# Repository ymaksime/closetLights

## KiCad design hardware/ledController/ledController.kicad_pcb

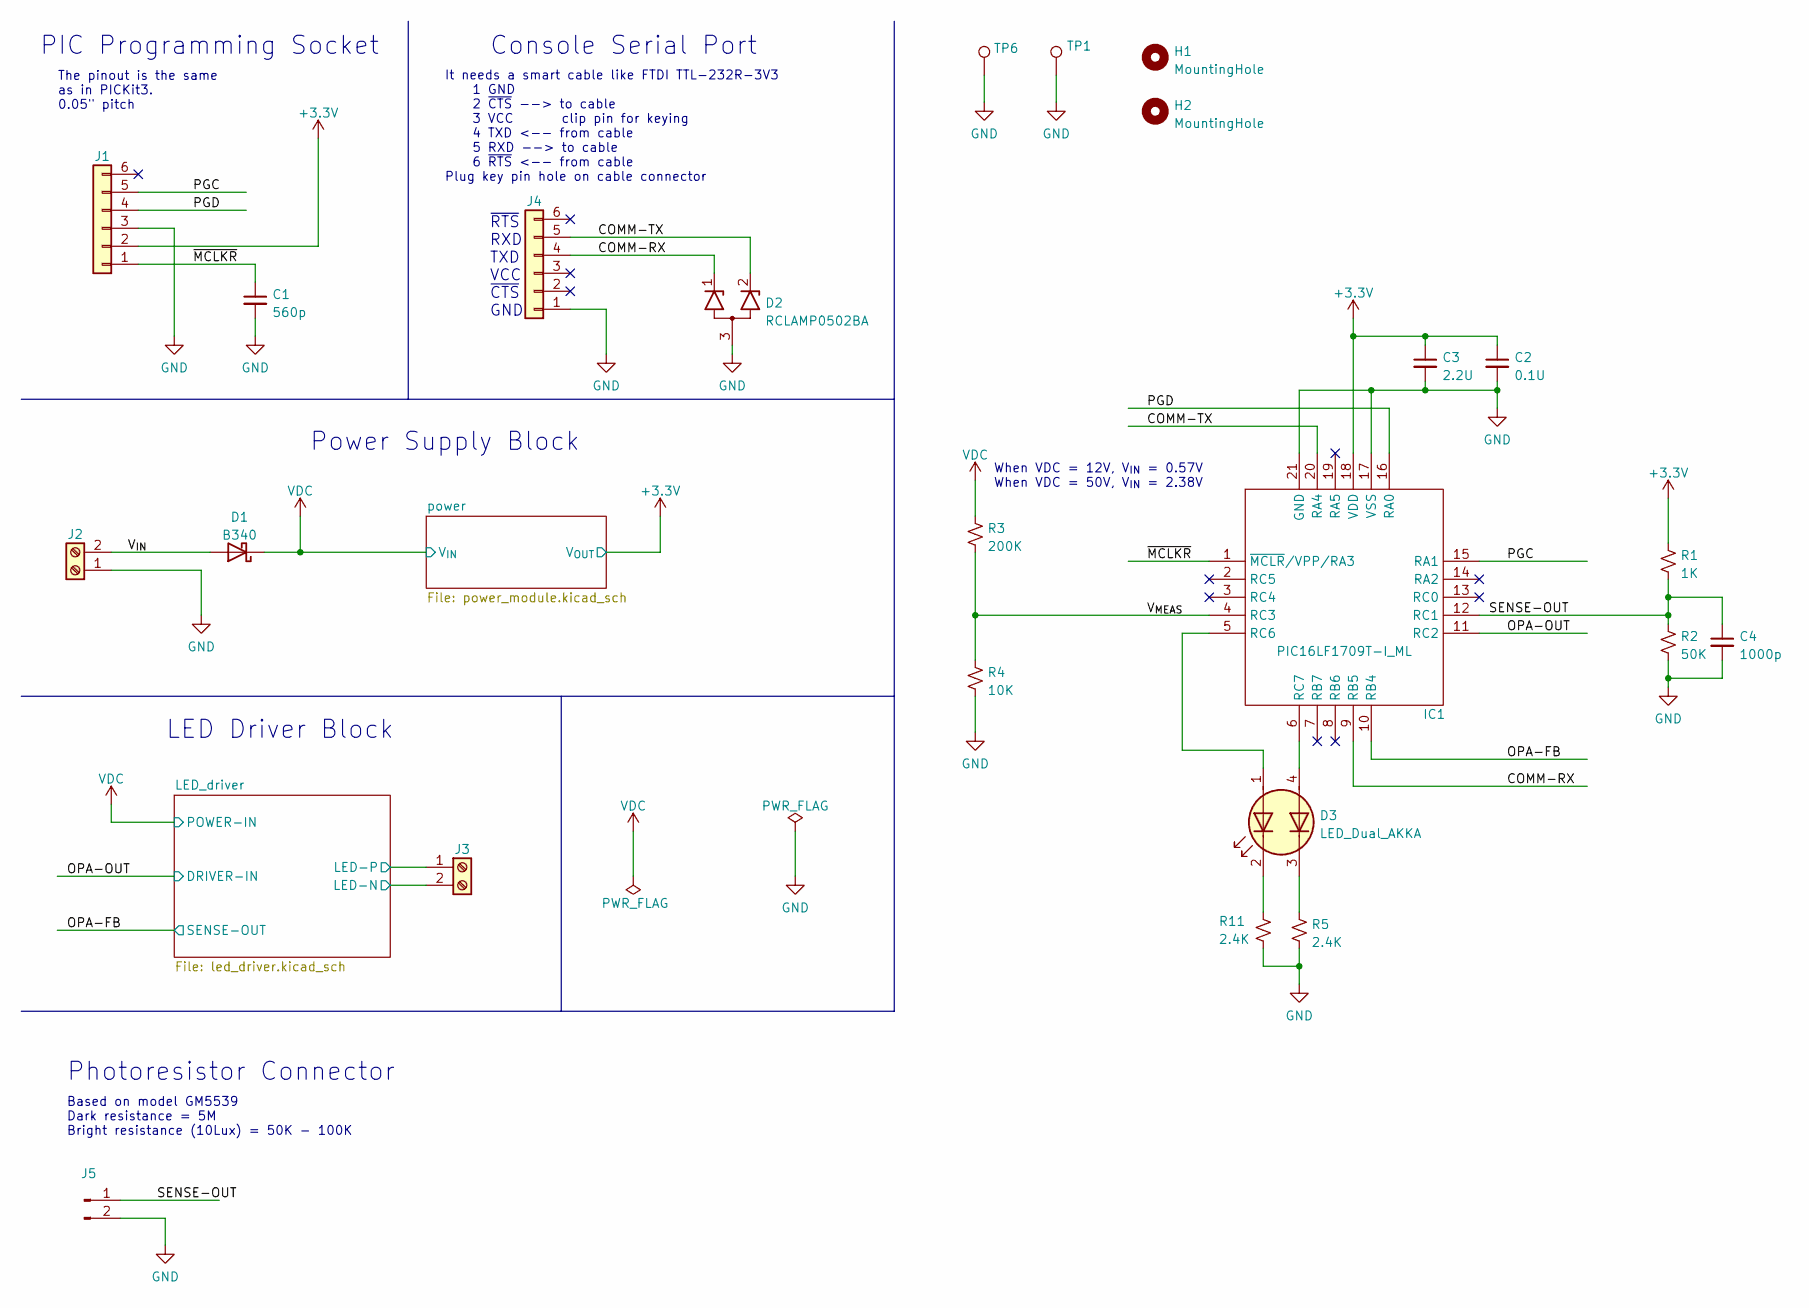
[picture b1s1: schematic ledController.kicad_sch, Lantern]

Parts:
C1: 560p; C_0402_1005Metric_Pad0.74x0.62mm_HandSolder
C2: 0.1U; C_0402_1005Metric_Pad0.74x0.62mm_HandSolder
C3: 2.2U; C_0402_1005Metric_Pad0.74x0.62mm_HandSolder
C4: 1000p; C_0402_1005Metric_Pad0.74x0.62mm_HandSolder
D1: B340; D_SMA
D2: RCLAMP0502BA; SC-75
D3: LED_Dual_AKKA; LED_Kingbright_APHBM2012_2x1.25mm
H1, H2: MountingHole; MountingHole_2.5mm_Pad_TopBottom
IC1: PIC16LF1709T-I_ML; QFN-20-1EP_4x4mm_P0.5mm_EP2.5x2.5mm
J1: Conn_01x06; PinHeader_1x06_P1.27mm_Vertical
J2, J3: Screw_Terminal_01x02; TerminalBlock_Altech_AK300-2_P5.00mm
J4: Conn_01x06; PinHeader_1x06_P2.54mm_Vertical
J5: Conn_01x02_Male; PinSocket_1x02_P2.54mm_Vertical
R1: 1K; R_0603_1608Metric_Pad0.98x0.95mm_HandSolder
R2: 50K; R_0603_1608Metric_Pad0.98x0.95mm_HandSolder
R3: 200K; R_0603_1608Metric_Pad0.98x0.95mm_HandSolder
R4: 10K; R_0603_1608Metric_Pad0.98x0.95mm_HandSolder
R5, R11: 2.4K; R_0603_1608Metric_Pad0.98x0.95mm_HandSolder
TP1, TP6: TestPoint; TestPoint_Pad_0.185in_x_0.135in

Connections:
+3.3V: C2.1, C3.1, IC1.18 (VDD), J1.2, R1.1; also elsewhere on the board
/COMM-RX: D2.1 (K1), IC1.9 (RB5), J4.4
/COMM-TX: D2.2 (K2), IC1.20 (RA4), J4.5
/LED_driver/LED-N: J3.2; also elsewhere on the board
/OPA-FB: IC1.10 (RB4); also elsewhere on the board
/OPA-OUT: IC1.11 (RC2); also elsewhere on the board
/PGC: IC1.15 (RA1), J1.5
/PGD: IC1.16 (RA0), J1.4
/SENSE-OUT: C4.1, IC1.12 (RC1), J5.1, R1.2, R2.1
/V_{IN}: D1.2 (A), J2.2
/V_{MEAS}: IC1.4 (RC3), R3.2, R4.1
/~MCLKR: C1.1, IC1.1 (~MCLR/VPP/RA3), J1.1
GND: C1.2, C2.2, C3.2, C4.2, D2.3 (A), IC1.17 (VSS), IC1.21 (GND), J1.3, J2.1, J4.1, J5.2, R2.2, R4.2, R5.2, R11.2, TP1.1, TP6.1; also elsewhere on the board
unnamed: D3.1 (A1), IC1.5 (RC6)
unnamed: D3.2 (K1), R11.1
unnamed: D3.3 (K2), R5.1
unnamed: D3.4 (A2), IC1.6 (RC7)
VDC: D1.1 (K), J3.1, R3.1; also elsewhere on the board

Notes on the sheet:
Photoresistor Connector
It needs a smart cable like FTDI TTL-232R-3V3 1 GND 2 ~{CTS} --> to cable 3 VCC clip pin for keying 4 TXD <-- from cable 5 RXD --> to cable 6 ~{RTS} <-- from cable Plug key pin hole on cable connector
~{RTS} RXD TXD VCC ~{CTS} GND
Power Supply Block
PIC Programming Socket
Console Serial Port
The pinout is the same as in PICKit3. 0.05" pitch
When VDC = 12V, V_{IN} = 0.57V When VDC = 50V, V_{IN} = 2.38V
Based on model GM5539 Dark resistance = 5M Bright resistance (10Lux) = 50K - 100K
LED Driver Block

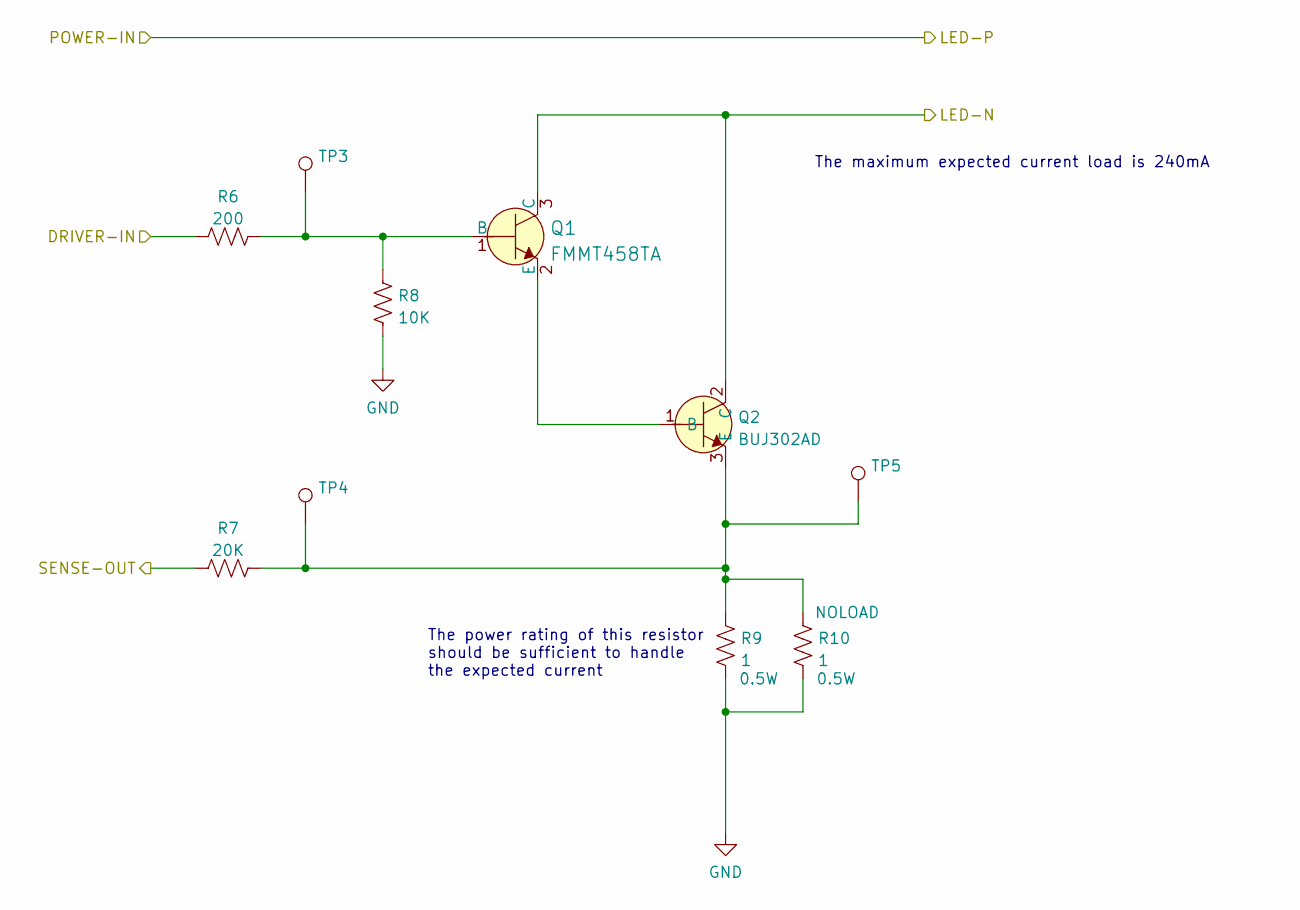
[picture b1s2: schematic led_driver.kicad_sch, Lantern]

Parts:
Q1: FMMT458TA; SOT-23-3; MPN FMMT458TA; Digi-Key_PN FMMT458CT-ND
Q2: BUJ302AD; SOT-428
R6: 200; R_0603_1608Metric_Pad0.98x0.95mm_HandSolder
R7: 20K; R_0603_1608Metric_Pad0.98x0.95mm_HandSolder
R8: 10K; R_0603_1608Metric_Pad0.98x0.95mm_HandSolder
R9, R10: 1; R_1206_3216Metric_Pad1.30x1.75mm_HandSolder
TP3, TP4, TP5: TestPoint; TestPoint_Pad_D1.5mm

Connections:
/LED_driver/LED-N: Q1.3 (C), Q2.2 (C); also elsewhere on the board
/OPA-FB: R7.1; also elsewhere on the board
/OPA-OUT: R6.1; also elsewhere on the board
GND: R8.2, R9.2, R10.2; also elsewhere on the board
unnamed: Q1.1 (B), R6.2, R8.1, TP3.1
unnamed: Q1.2 (E), Q2.1 (B)
unnamed: Q2.3 (E), R7.2, R9.1, R10.1, TP4.1, TP5.1

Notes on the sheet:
The maximum expected current load is 240mA
The power rating of this resistor should be sufficient to handle the expected current

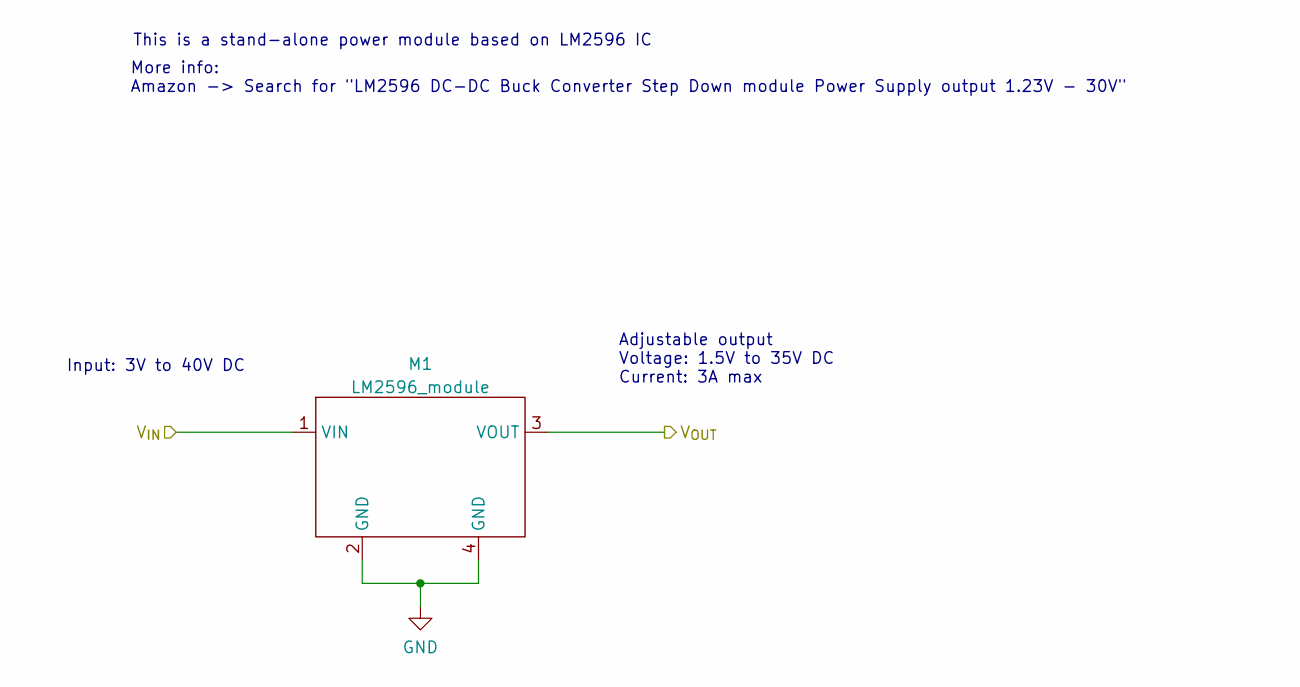
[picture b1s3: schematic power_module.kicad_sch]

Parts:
M1: LM2596_module

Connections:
+3.3V: M1.3 (VOUT); also elsewhere on the board
GND: M1.2 (GND), M1.4 (GND); also elsewhere on the board
VDC: M1.1 (VIN); also elsewhere on the board

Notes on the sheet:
Adjustable output Voltage: 1.5V to 35V DC Current: 3A max
Input: 3V to 40V DC
This is a stand-alone power module based on LM2596 IC
More info: Amazon -> Search for "LM2596 DC-DC Buck Converter Step Down module Power Supply output 1.23V - 30V"

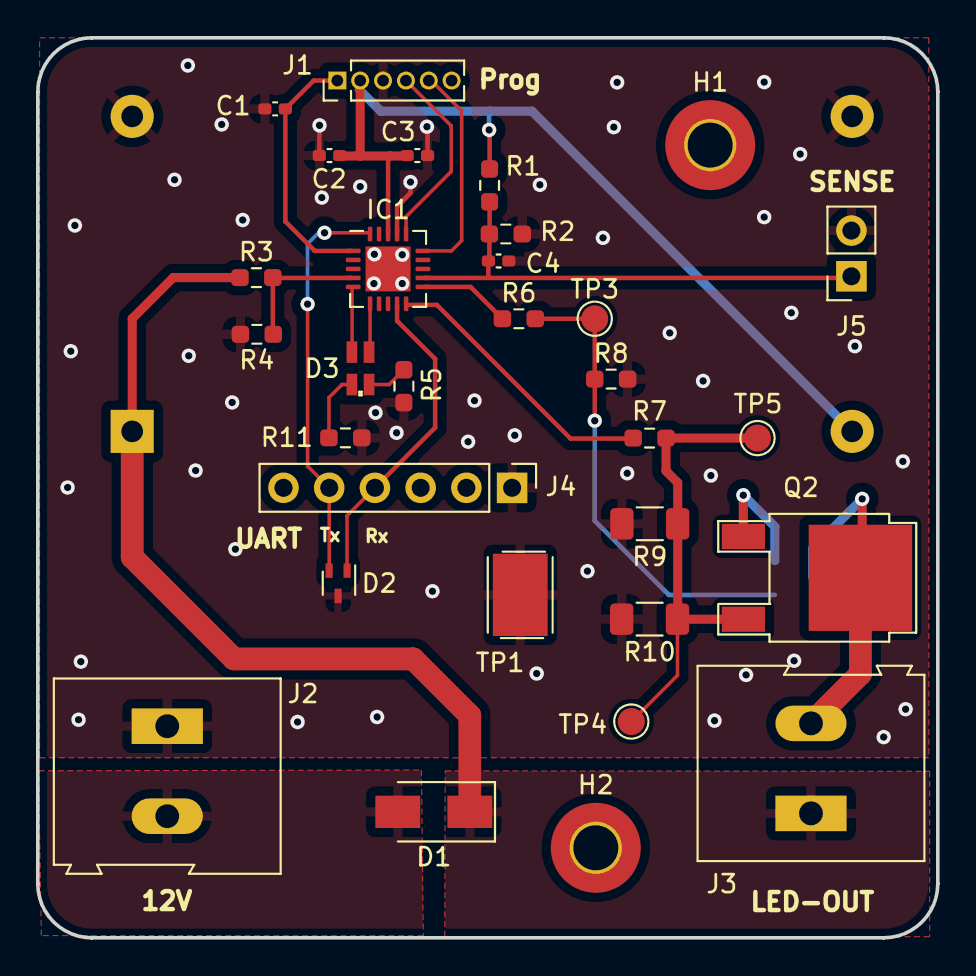
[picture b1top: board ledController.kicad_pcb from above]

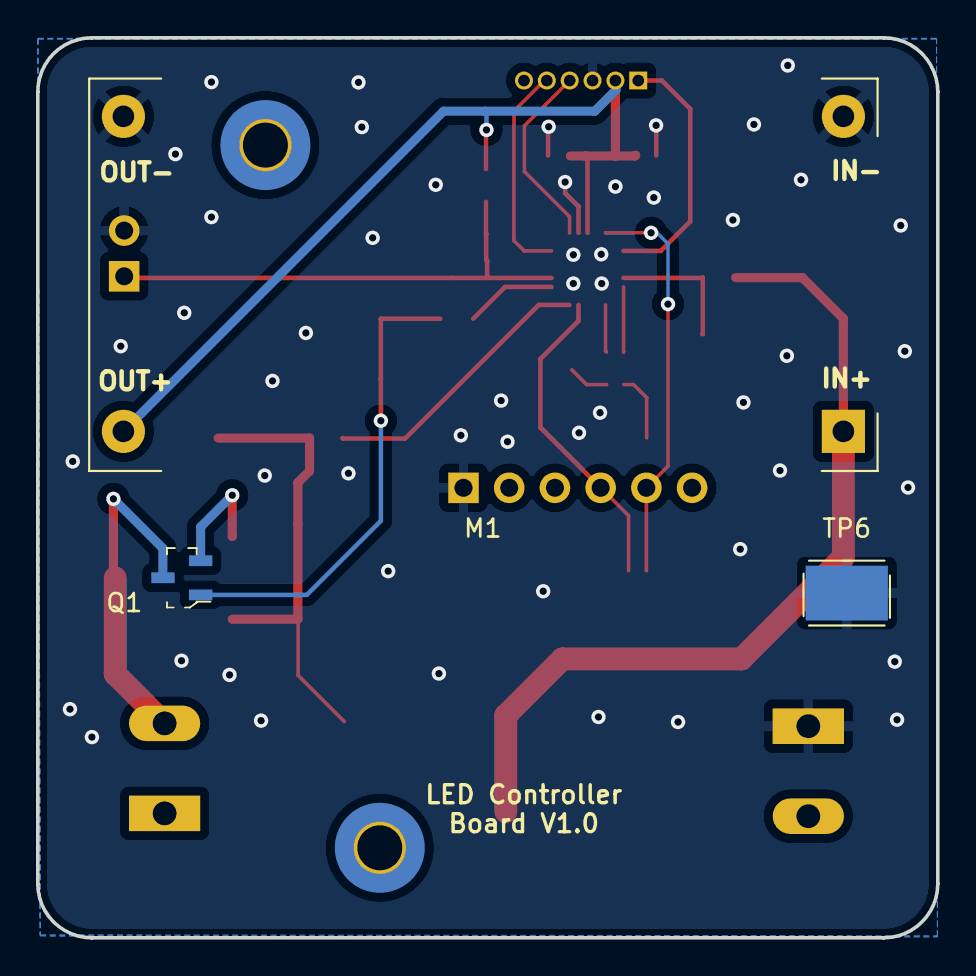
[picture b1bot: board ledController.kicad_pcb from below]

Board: 2 copper layers, 50.0 x 50.0 mm, 34 parts (3 on the bottom side), 21 nets.

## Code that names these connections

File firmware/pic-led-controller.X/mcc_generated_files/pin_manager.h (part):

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#define RA4_SetHigh()            do { LATAbits.LATA4 = 1; } while(0)
#define RA4_SetLow()             do { LATAbits.LATA4 = 0; } while(0)
#define RA4_Toggle()             do { LATAbits.LATA4 = ~LATAbits.LATA4; } while(0)
#define RA4_GetValue()              PORTAbits.RA4
#define RA4_SetDigitalInput()    do { TRISAbits.TRISA4 = 1; } while(0)
#define RA4_SetDigitalOutput()   do { TRISAbits.TRISA4 = 0; } while(0)
#define RA4_SetPullup()             do { WPUAbits.WPUA4 = 1; } while(0)
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#define RB4_SetHigh()            do { LATBbits.LATB4 = 1; } while(0)
#define RB4_SetLow()             do { LATBbits.LATB4 = 0; } while(0)
#define RB4_Toggle()             do { LATBbits.LATB4 = ~LATBbits.LATB4; } while(0)
#define RB4_GetValue()              PORTBbits.RB4
#define RB4_SetDigitalInput()    do { TRISBbits.TRISB4 = 1; } while(0)
#define RB4_SetDigitalOutput()   do { TRISBbits.TRISB4 = 0; } while(0)
#define RB4_SetPullup()             do { WPUBbits.WPUB4 = 1; } while(0)
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#define RB5_SetHigh()            do { LATBbits.LATB5 = 1; } while(0)
#define RB5_SetLow()             do { LATBbits.LATB5 = 0; } while(0)
#define RB5_Toggle()             do { LATBbits.LATB5 = ~LATBbits.LATB5; } while(0)
#define RB5_GetValue()              PORTBbits.RB5
#define RB5_SetDigitalInput()    do { TRISBbits.TRISB5 = 1; } while(0)
#define RB5_SetDigitalOutput()   do { TRISBbits.TRISB5 = 0; } while(0)
#define RB5_SetPullup()             do { WPUBbits.WPUB5 = 1; } while(0)
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// get/set sensor aliases
#define sensor_TRIS                 TRISCbits.TRISC1
#define sensor_LAT                  LATCbits.LATC1
#define sensor_PORT                 PORTCbits.RC1
#define sensor_WPU                  WPUCbits.WPUC1
#define sensor_OD                   ODCONCbits.ODC1
#define sensor_ANS                  ANSELCbits.ANSC1
#define sensor_SetHigh()            do { LATCbits.LATC1 = 1; } while(0)
#define sensor_SetLow()             do { LATCbits.LATC1 = 0; } while(0)
#define sensor_Toggle()             do { LATCbits.LATC1 = ~LATCbits.LATC1; } while(0)
#define sensor_GetValue()           PORTCbits.RC1
#define sensor_SetDigitalInput()    do { TRISCbits.TRISC1 = 1; } while(0)
#define sensor_SetDigitalOutput()   do { TRISCbits.TRISC1 = 0; } while(0)
#define sensor_SetPullup()          do { WPUCbits.WPUC1 = 1; } while(0)
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#define RC2_SetHigh()            do { LATCbits.LATC2 = 1; } while(0)
#define RC2_SetLow()             do { LATCbits.LATC2 = 0; } while(0)
#define RC2_Toggle()             do { LATCbits.LATC2 = ~LATCbits.LATC2; } while(0)
#define RC2_GetValue()              PORTCbits.RC2
#define RC2_SetDigitalInput()    do { TRISCbits.TRISC2 = 1; } while(0)
#define RC2_SetDigitalOutput()   do { TRISCbits.TRISC2 = 0; } while(0)
#define RC2_SetPullup()             do { WPUCbits.WPUC2 = 1; } while(0)
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// get/set vMeas aliases
#define vMeas_TRIS                 TRISCbits.TRISC3
#define vMeas_LAT                  LATCbits.LATC3
#define vMeas_PORT                 PORTCbits.RC3
#define vMeas_WPU                  WPUCbits.WPUC3
#define vMeas_OD                   ODCONCbits.ODC3
#define vMeas_ANS                  ANSELCbits.ANSC3
#define vMeas_SetHigh()            do { LATCbits.LATC3 = 1; } while(0)
#define vMeas_SetLow()             do { LATCbits.LATC3 = 0; } while(0)
#define vMeas_Toggle()             do { LATCbits.LATC3 = ~LATCbits.LATC3; } while(0)
#define vMeas_GetValue()           PORTCbits.RC3
#define vMeas_SetDigitalInput()    do { TRISCbits.TRISC3 = 1; } while(0)
#define vMeas_SetDigitalOutput()   do { TRISCbits.TRISC3 = 0; } while(0)
#define vMeas_SetPullup()          do { WPUCbits.WPUC3 = 1; } while(0)
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// get/set ledRed aliases
#define ledRed_TRIS                 TRISCbits.TRISC6
#define ledRed_LAT                  LATCbits.LATC6
#define ledRed_PORT                 PORTCbits.RC6
#define ledRed_WPU                  WPUCbits.WPUC6
#define ledRed_OD                   ODCONCbits.ODC6
#define ledRed_ANS                  ANSELCbits.ANSC6
#define ledRed_SetHigh()            do { LATCbits.LATC6 = 1; } while(0)
#define ledRed_SetLow()             do { LATCbits.LATC6 = 0; } while(0)
#define ledRed_Toggle()             do { LATCbits.LATC6 = ~LATCbits.LATC6; } while(0)
#define ledRed_GetValue()           PORTCbits.RC6
#define ledRed_SetDigitalInput()    do { TRISCbits.TRISC6 = 1; } while(0)
#define ledRed_SetDigitalOutput()   do { TRISCbits.TRISC6 = 0; } while(0)
#define ledRed_SetPullup()          do { WPUCbits.WPUC6 = 1; } while(0)
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// get/set ledGrn aliases
#define ledGrn_TRIS                 TRISCbits.TRISC7
#define ledGrn_LAT                  LATCbits.LATC7
#define ledGrn_PORT                 PORTCbits.RC7
#define ledGrn_WPU                  WPUCbits.WPUC7
#define ledGrn_OD                   ODCONCbits.ODC7
#define ledGrn_ANS                  ANSELCbits.ANSC7
#define ledGrn_SetHigh()            do { LATCbits.LATC7 = 1; } while(0)
#define ledGrn_SetLow()             do { LATCbits.LATC7 = 0; } while(0)
#define ledGrn_Toggle()             do { LATCbits.LATC7 = ~LATCbits.LATC7; } while(0)
#define ledGrn_GetValue()           PORTCbits.RC7
#define ledGrn_SetDigitalInput()    do { TRISCbits.TRISC7 = 1; } while(0)
#define ledGrn_SetDigitalOutput()   do { TRISCbits.TRISC7 = 0; } while(0)
#define ledGrn_SetPullup()          do { WPUCbits.WPUC7 = 1; } while(0)
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
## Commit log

2022-09-26 initial board checkin
2022-09-26 more files to ignore
2022-09-26 info about additional libriries
2022-10-06 Some technical info about the LED strip light
2022-10-06 Added two more schematic pages
2022-10-07 Updated max LED current
2022-10-07 Added LTSpice simulations current driver
2022-10-07 Added theoretical ON resistance at max current
2022-10-10 Updated library tables to include custom library
2022-10-14 Few mods to the simulation files
2022-10-14 Added new schematic page for led current driver
2022-10-14 Incorporated the led driver to the main design
2022-10-21 Added serial comm
2022-10-27 Renamed and modified power sheet
2022-10-27 Added one more design for 3.3V switcher
2022-10-27 Some cleanup
2022-10-27 Added BJT base resistor and some cleanup
2022-10-27 Putting everything together
2022-11-01 Added NOLOAD resistor R10
2022-12-09 Added a datasheet for PIR censor
2022-12-09 Update gitignore
2022-12-21 Added new schematic for power module
2022-12-21 First attempt of schematic to PCB
2022-12-29 More schematic updates
    Moved from PIR sensor to photoresistor + additional components
    Added mounting holes
    Moved to a stand alone 3.3V switcher
2022-12-29 PCB work
2022-12-29 Minor changes
2022-12-29 Changed R9 and R10 to use 1206
2022-12-29 Replaced debug LED
2022-12-30 modified footprint for D1
2022-12-30 Replaced footprint of D2
2022-12-30 Changed based on the footprint updates
2022-12-30 Minor changes in the simulations
2023-01-06 Initial commit for PIC firmware
2023-01-09 Device change
    Changed from PIC16F1769 to PIC16LF1709
2023-01-09 New datasheets
2023-01-10 Version V1.1
    Replaced PIC16F1769 with PIC16LF1709. They are pin-to-pin
    compatible with each other
2023-04-05 Added support for RS232 communication
    Also added a few function to control LEDs and read ADC channels
    for sensor and +12V voltage
2023-04-05 Fixed the note for Serial Port connector
2023-04-05 Changed R1 from 1K to 15K
    Based on the experiments, R1 needs to be close to 15K
2023-04-12 Added support for ADC read functions
    Added the following RS232 functions
    ADC5
    * Sets channel 5 as an active ADC channel
    * This channel measure SENSOR-OUT signal, which is photo-resistor
    output
    ADC7
2023-08-31 Added DAC control functions
    DACS
    Allows a user to set DAC to a specific value through RS232 interface.
    The value must be in decimal format and should not exceed 8-bit value
    If larger than an 8-bit value, it will be truncated
    Expected command format: DACS XXX
    DACR
2023-08-31 Function name change
    Renamed "read_millivolts()" to "adc_read" since it is just averaged out
    ADC reading
2023-09-01 Forgot to include for DAC
2023-09-01 Better comments with formula
2023-09-01 Initial work PV scripts
2023-09-05 Store only valid characters
2023-09-05 Added ECHO command
    When interfacing with the module using python scripts, we need to turn
    OFF the echo feature otherwise it becomes difficult to parse the output
2023-09-05 forgot about the header
2023-09-06 Bug fix
    There was a typo which resulted in setting a wrong baud rate. Also
    removed unused code
2023-09-06 New commands and bug fixes
    Fixed read and write function based on the experiments
    Added control for ECHO command
    Added DAC set command
    Improved comments to include formulas
2023-09-06 Sandbox
2023-09-06 New simulation file for BJT
2023-09-06 Ignore .log and .raw files
2023-09-06 Ignore build and dist directories
2023-09-13 Modifications to the generated DAC file
    By default if the DAC is set to 0, the OP-AMP is still sourcing a small
    amount of current which slightly turns On the external transistor.
    Therefore, if zero is requested, convert the OP-AMP into a follower to
    eliminate the problem
2023-09-13 Added formula for DAC-Current relationship
2023-09-13 Moved LED related code into a separate file
2023-09-13 Improved ADC channel selection mechanism
2023-09-19 Code restructure and new function
    Moved the code around to get a better structure
    Added light_contol functions
2023-09-19 Added comments
2023-09-19 Added Word file with some technical info
2023-09-19 Minor changes Python script
2023-09-19 New Python scripts
2023-09-19 Random files
2023-09-19 Begin working on FW for new HW
    Removed obsolete functions (no DAC)
    Added PWM functionality and additional Timer
2023-09-20 Modified LITE command to control LED intensity
    * Disabled Timer6 on power-on
    * LITE command now takes 0-999 value for ligth intensity
    * Added "soft" power-on and power-down feature
2023-09-20 Added Timer_1 with 100ms period
2023-09-22 Use sensor ADC channel as default
2023-09-22 Initial cut of the light control state-machine
2023-10-04 Adapted the firmware for the hardware changes
    This version of firmware is used for the following hardware changes:
    * The light dimming is implemented using PWM feature and a MOSFET
    * The ON/OFF switch is implemented using a capacitive sensor
    FW changes:
    * The light is controlled directly by a capacitive sensor
    * ADC monitors only the vMeas channel

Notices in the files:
firmware/pic-led-controller.X/mcc_generated_files/pin_manager.h:
(c) 2018 Microchip Technology Inc. and its subsidiaries.
